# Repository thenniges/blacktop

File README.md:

# Blacktop
When cloning this project you need to make some additional git commands to get the unity unit test framework and cmock mock framework

cd blacktop

git submodule init

git submodule update

# Test scripts

There is a test script in the blacktop directory that will run unit tests every time that you save any of the source code. It will run all the unit tests for all subdirectories.

In order to use it you need to install a python tool called when-changed. The command is:

pip install when-changed

Run it in the blacktop directory using the following command:

./watchtests.sh

There is also a system test script in the test folder that can be ran using the following command:

./runtest.sh

# Directories

license: contains the relevant license files for this project

standards: contains the coding standards that should be followed for this project

src: contains the source code and appropriate tests for this project

doc: contains the documentation for this project

spikes: contains spikes that have been done to understand how this project will work

hw: contails kicad files defining the hardware design

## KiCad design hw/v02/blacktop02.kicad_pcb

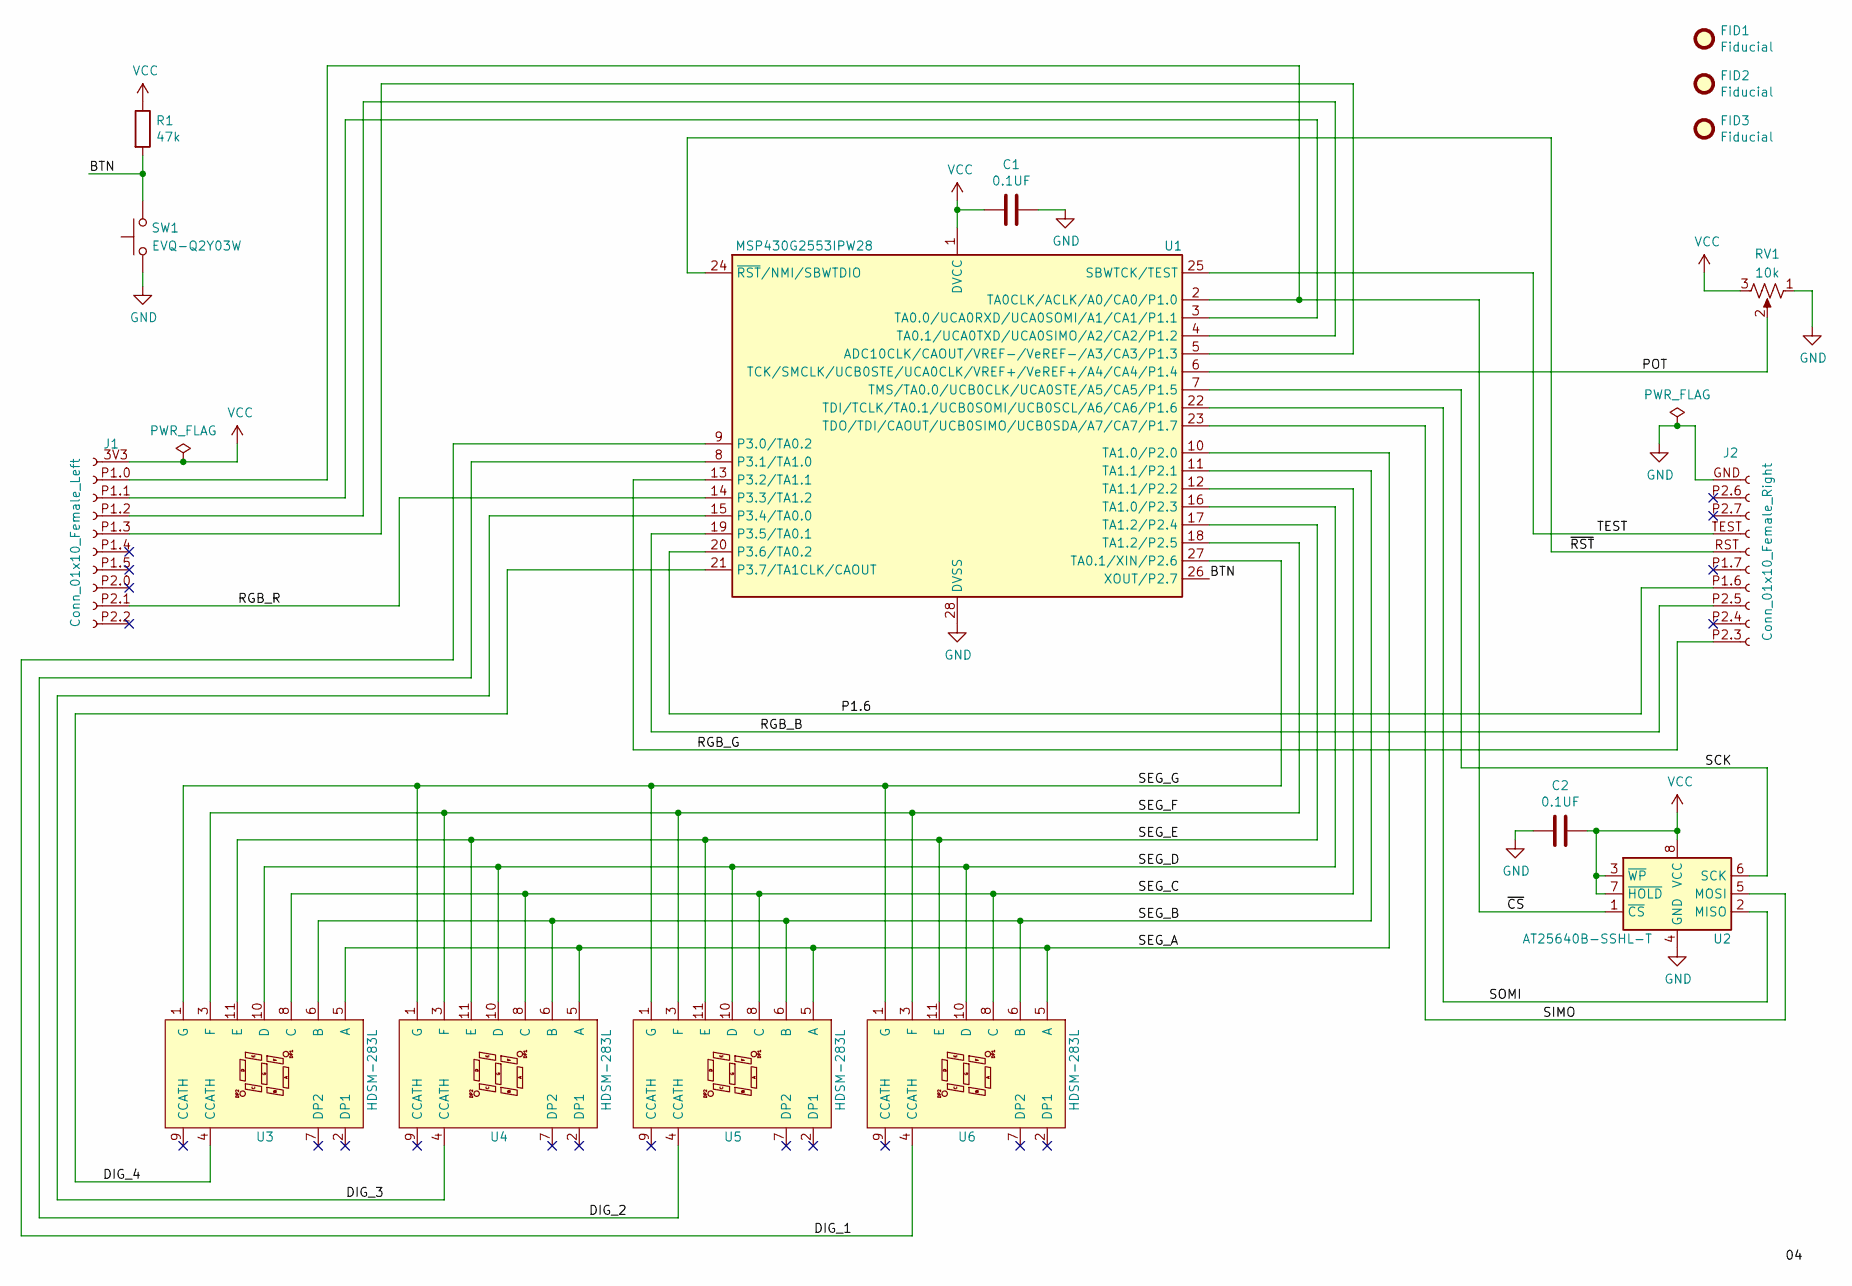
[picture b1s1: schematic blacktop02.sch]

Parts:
C1, C2: 0.1UF; C_0603_1608Metric_Pad1.05x0.95mm_HandSolder
FID1, FID2, FID3: Fiducial; Fiducial_0.75mm_Mask1.5mm
J1: Conn_01x10_Female_Left; PinSocket_1x10_P2.54mm_Vertical_Left
J2: Conn_01x10_Female_Right; PinSocket_1x10_P2.54mm_Vertical_Right
R1: 47k; R_0603_1608Metric_Pad1.05x0.95mm_HandSolder
RV1: 10k; PTV09A-4020U-B103
SW1: EVQ-Q2Y03W; SW_SPST_EVQQ2
U1: MSP430G2553IPW28; TSSOP-28_4.4x9.7mm_P0.65mm
U2: AT25640B-SSHL-T; SOIC-8_3.9x4.9mm_P1.27mm
U3, U4, U5, U6: HDSM-283L

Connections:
/BTN: R1.2, SW1.2, U1.26 (XOUT/P2.7)
/DIG_1: U1.9 (P3.0/TA0.2), U6.4 (CCATH)
/DIG_2: U1.8 (P3.1/TA1.0), U5.4 (CCATH)
/DIG_3: U1.15 (P3.4/TA0.0), U4.4 (CCATH)
/DIG_4: U1.21 (P3.7/TA1CLK/CAOUT), U3.4 (CCATH)
/P1.6: J2.P1.6 (Pin_14), U1.20 (P3.6/TA0.2)
/POT: RV1.2, U1.6 (TCK/SMCLK/UCB0STE/UCA0CLK/VREF+/VeREF+/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)
/RGB_B: J2.P2.5 (Pin_13), U1.19 (P3.5/TA0.1)
/RGB_G: J2.P2.3 (Pin_11), U1.13 (P3.2/TA1.1)
/RGB_R: J1.P2.1 (Pin_9), U1.14 (P3.3/TA1.2)
/SCK: U1.7 (TMS/TA0.0/UCB0CLK/UCA0STE/A5/CA5/P1.5), U2.6 (SCK)
/SEG_A: U1.10 (TA1.0/P2.0), U3.5 (A), U4.5 (A), U5.5 (A), U6.5 (A)
/SEG_B: U1.11 (TA1.1/P2.1), U3.6 (B), U4.6 (B), U5.6 (B), U6.6 (B)
/SEG_C: U1.12 (TA1.1/P2.2), U3.8 (C), U4.8 (C), U5.8 (C), U6.8 (C)
/SEG_D: U1.16 (TA1.0/P2.3), U3.10 (D), U4.10 (D), U5.10 (D), U6.10 (D)
/SEG_E: U1.17 (TA1.2/P2.4), U3.11 (E), U4.11 (E), U5.11 (E), U6.11 (E)
/SEG_F: U1.18 (TA1.2/P2.5), U3.3 (F), U4.3 (F), U5.3 (F), U6.3 (F)
/SEG_G: U1.27 (TA0.1/XIN/P2.6), U3.1 (G), U4.1 (G), U5.1 (G), U6.1 (G)
/SIMO: U1.23 (TDO/TDI/CAOUT/UCB0SIMO/UCB0SDA/A7/CA7/P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), U2.5 (MOSI)
/SOMI: U1.22 (TDI/TCLK/TA0.1/UCB0SOMI/UCB0SCL/A6/CA6/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), U2.2 (MISO)
/TEST: J2.TEST (Pin_17), U1.25 (SBWTCK/TEST)
/~CS: J1.P1.0 (Pin_2), U1.2 (TA0CLK/ACLK/A0/CA0/P1.0), U2.1 (~CS)
/~RST: J2.~RST (Pin_16), U1.24 (~RST~/NMI/SBWTDIO)
GND: C1.1, C2.2, J2.GND (Pin_20), RV1.1, SW1.1, U1.28 (DVSS), U2.4 (GND)
unnamed: J1.P1.1 (Pin_3), U1.3 (TA0.0/UCA0RXD/UCA0SOMI/A1/CA1/P1.1)
unnamed: J1.P1.2 (Pin_4), U1.4 (TA0.1/UCA0TXD/UCA0SIMO/A2/CA2/P1.2)
unnamed: J1.P1.3 (Pin_5), U1.5 (ADC10CLK/CAOUT/VREF-/VeREF-/A3/CA3/P1.3)
VCC: C1.2, C2.1, J1.3V3 (Pin_1), R1.1, RV1.3, U1.1 (DVCC), U2.3 (~WP), U2.7 (~HOLD), U2.8 (VCC)

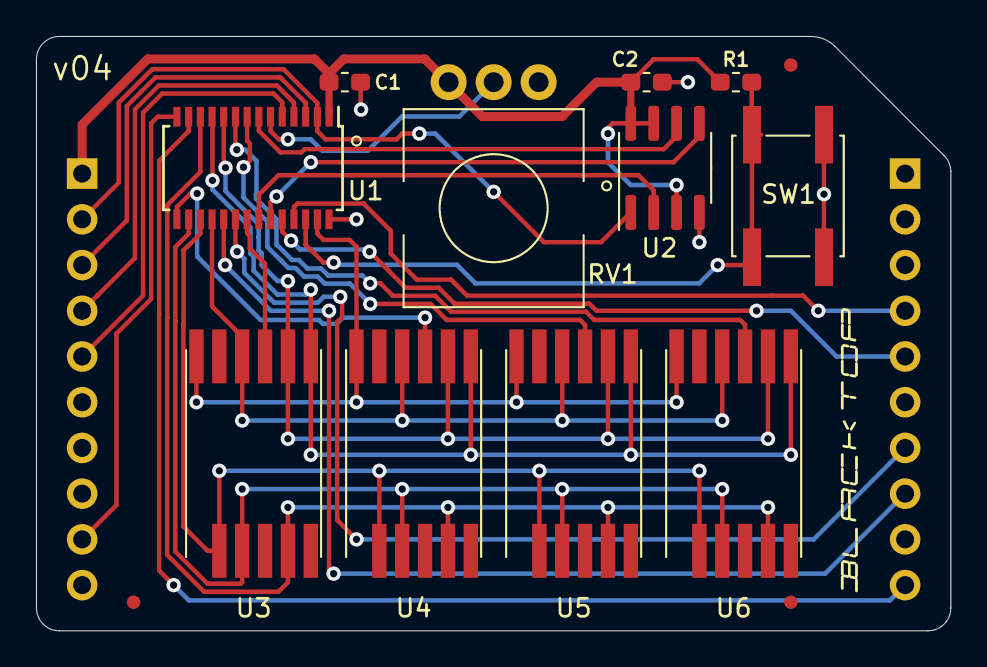
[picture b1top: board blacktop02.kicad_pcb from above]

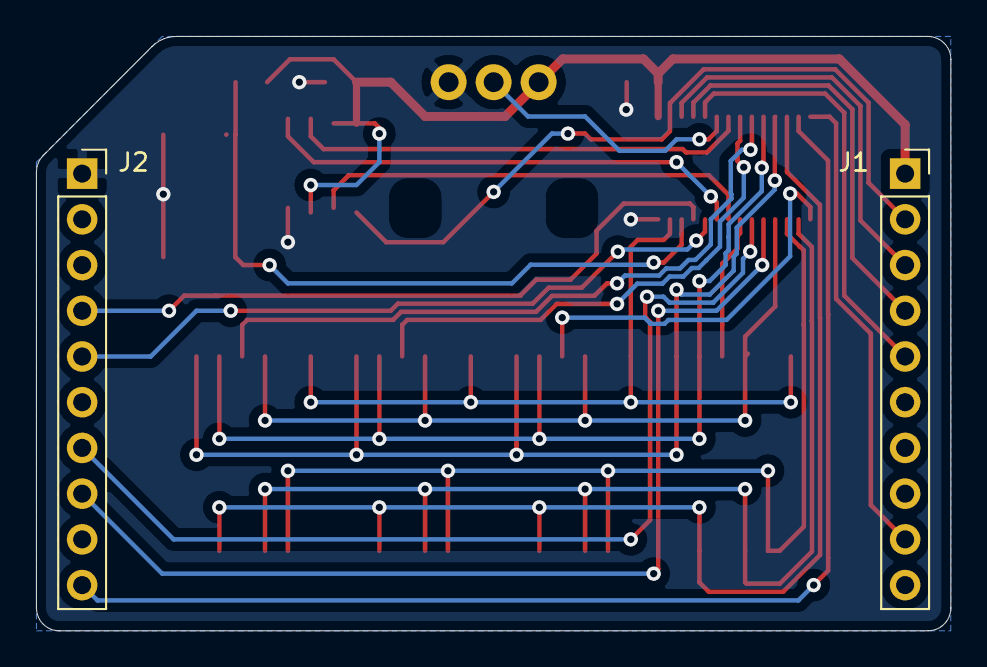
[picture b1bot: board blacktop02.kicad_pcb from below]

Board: 2 copper layers, 50.8 x 33.0 mm, 16 parts (2 on the bottom side), 28 nets.

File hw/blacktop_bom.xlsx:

Make | Item | Description | Source | Qty | $/unit @ 100+ | Unit Total
TI | MSP430G2553IPW28R | Microcontroller w/ 3 8-bit GPIO ports, TSSOP-28 | Mouser/DK | 1.0 | 1.67 | 1.67
Broadcom | HDSM-283L | 7-seg digit, 7mm orange, common cathode, SMD | Mouser/DK | 4.0 | 1.3 | 5.2
Panasonic | EVQ-Q2Y03W | momentary button, SMD | SBA | 1.0 | 0.2549 | 0.2549
Microchip | AT25640B-SSHL-T | 64kbit SPI EEPROM, SOIC-8 | Mouser/DK | 1.0 | 0.422 | 0.422
Murata |  | CAP CER 0.1UF 25V 10% X7R 0603 | SBA | 2.0 | 0.28 | 0.56
Bourns | PTV09A-4015U-B103 | 10k pot, top 6mm shaft, through-hole | Mouser/DK | 1.0 | 0.62 | 0.62
Samtech | CES-110-01-G-S | Headers .100" Closed Entry Low Profile Socket Strip | Mouser/DK | 2.0 | 1.72 | 3.44
PCB |  |  | OSHPark | 2.6 | 1.0 | 2.6
assembly |  |  | SBA | 1.0 | 3.65 | 3.65
 |  |  |  |  |  | 18.4169

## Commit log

2019-10-10 Setup general repository structure
2019-10-10 Added a file discussing resources for SPI
2019-10-10 Left over from an old project, removed it
2019-10-28 Created a document with his expectations for our test plan
2019-10-28 removed doc that was meant for other repo
2019-11-07 Create LICENSE
2019-11-07 Moved the license to the license folder and removed placeholder
2019-11-07 Added git, unit test, and local programming standards
2019-11-07 Stories and TPS reports added to doc folder in their respective subfolders
2019-12-04 Updated standards and added an automation standard
2019-12-04 Made minor changes to git standard formatting
2019-12-10 Changed automation_standard.txt to AutomationStandard.txt and changed git_standard.txt to VersionControlStandard.txt
2019-12-11 Added a local programming standard
2019-12-11 Added the System test standard that Kahrl wrote
2020-02-06 version 01 of the pcb, ordered 2020-01-27
2020-02-06 version 2, ordered 2020-01-30
2020-02-07 added hw directory note
2020-02-15 Added a gitignore file
2020-02-15 Added the load test files needed to flash board
2020-02-15 Added .hex to gitignore
2020-02-15 Made changes to makefile so that you can just run make flash without running make first
2020-02-15 Made changes so that the red and green leds on the pcb are on
2020-02-15 Created a test program to test the new board
2020-02-15 Added the submodules for testing
2020-02-15 Added the test scripts and readme info on how to use
2020-02-15 v03 RC1 (rename is nontrivial so use v02 dir)
2020-02-16 Added functionality to the test program to allow the pontentiometer to change the red value of the rgb
2020-02-16 Updated the readme for test_program to reflect changes
2020-02-17 moved RV1 pin3 from pin2 to GND
2020-02-17 v03 final, prototypes ordered 2020-02-17
2020-02-20 Made changes for PCB 7segs
2020-02-21 Made it so that the 7seg cycles through 0-f for each digit
2020-03-23 Spikes from previous fork were added
2020-03-23 Tps reports and stories from old fork added
2020-03-23 All TPS Reports are up to date
2020-03-23 Stories are up to date
2020-03-23 a textfile with a linke to the youtube video of the finished board running was added to spikes
2020-03-27 Moved test program from spikes to src
2020-03-27 Initial commit of EEPROM_Driver
2020-03-27 wrote the main and finished the write function
2020-03-29 Finished read function and got SPI driver working
2020-03-31 TPS and Stories added
2020-04-05 Overhauled the EEPROM SPI driver
2020-04-07 TPS Report and Stories added
2020-04-07 Added and tested an erase function at the request of the client
2020-04-08 Developed and tested BlockRead and PageWrite functions
2020-04-08 Changed interface to eepromRead function and did light refactoring
2020-04-08 Updated EEPROM documentation
2020-04-08 Added a missing semicolon
2020-04-13 TPS Reports and Stories Updated
2020-04-17 Made a minor change to the init function to initialize the EEPTOM
2020-04-17 Moved unity and cmock to the lib folder
2020-04-17 Temporarily removed cmock and unity to put back as submodules
2020-04-17 Added CMock and Unity back as submodules
2020-04-18 Tied eeprom 3 and 7 to VCC, board v04 RC
2020-04-20 Added PDF of v04 schematic
2020-04-22 Updated git ignore
2020-04-22 Changed from Unity and CMock to googletest and fff
2020-04-22 Started unit testing
2020-04-22 Added to .gitignore
2020-04-22 Reupdated .gitignore to disclude eepromTests
2020-04-22 Fixed paths to unit test stuff
2020-04-22 Completed unit testing and coverage testing and updated watchtests
2020-04-22 TPS Report and stories updated
2020-04-24 Improved documentation of the repo
2020-04-24 Added readme for unit tests
2020-04-24 Made change to debug rule
2020-04-24 Added Erron's use cases to spikes
2020-04-24 Added test jig cad and BOM
2020-05-06 Removed all of the assignment files
2020-05-28 added hardware pullup (R1) to BTN
